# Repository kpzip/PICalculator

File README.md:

# *Award Winning* PICalculator
calculator made using super ancient PIC μController.

# Past customers have said:
"Fairly risky project that will depend a lot on the development environment. Not clear why 74HC138 will help read the buttons (could probably use SR for same purpose).         need to check what exists in terms of development environment    "This group chose the hardware as they "wanted a challenge". They are definitely one of the smarter groups in my section so I don't have much doubt that they will get it done. 

If you guys do think the hardware is more complex than neccesary, I'm sure they'd be okay with changing out the parts list."    "Are these people really experienced or did they find this project online? If the former, will all group members be able to contribute?

PIC16C74 likely does not have Arduino support. "ARM Cortex M4" is vague and any bare chip will likely only come in an SMD package. Both need a special programmer and special compiler setups. Would need to make a custom PCB or buy a dev board.

Why not just do everything in the M4 since it's vastly more powerful than the PIC?"    Looks like a very challenging project. I am not sure if all group members can contribute if they decide to go with this idea. I think one or two group members are pretty advanced. I feel like it would be hard to provide help to them since most mentors dont have experience with this microcontroller and it requires a different development environment.     Fairly sophisticated, were having issues with some operations outputting the wrong values"

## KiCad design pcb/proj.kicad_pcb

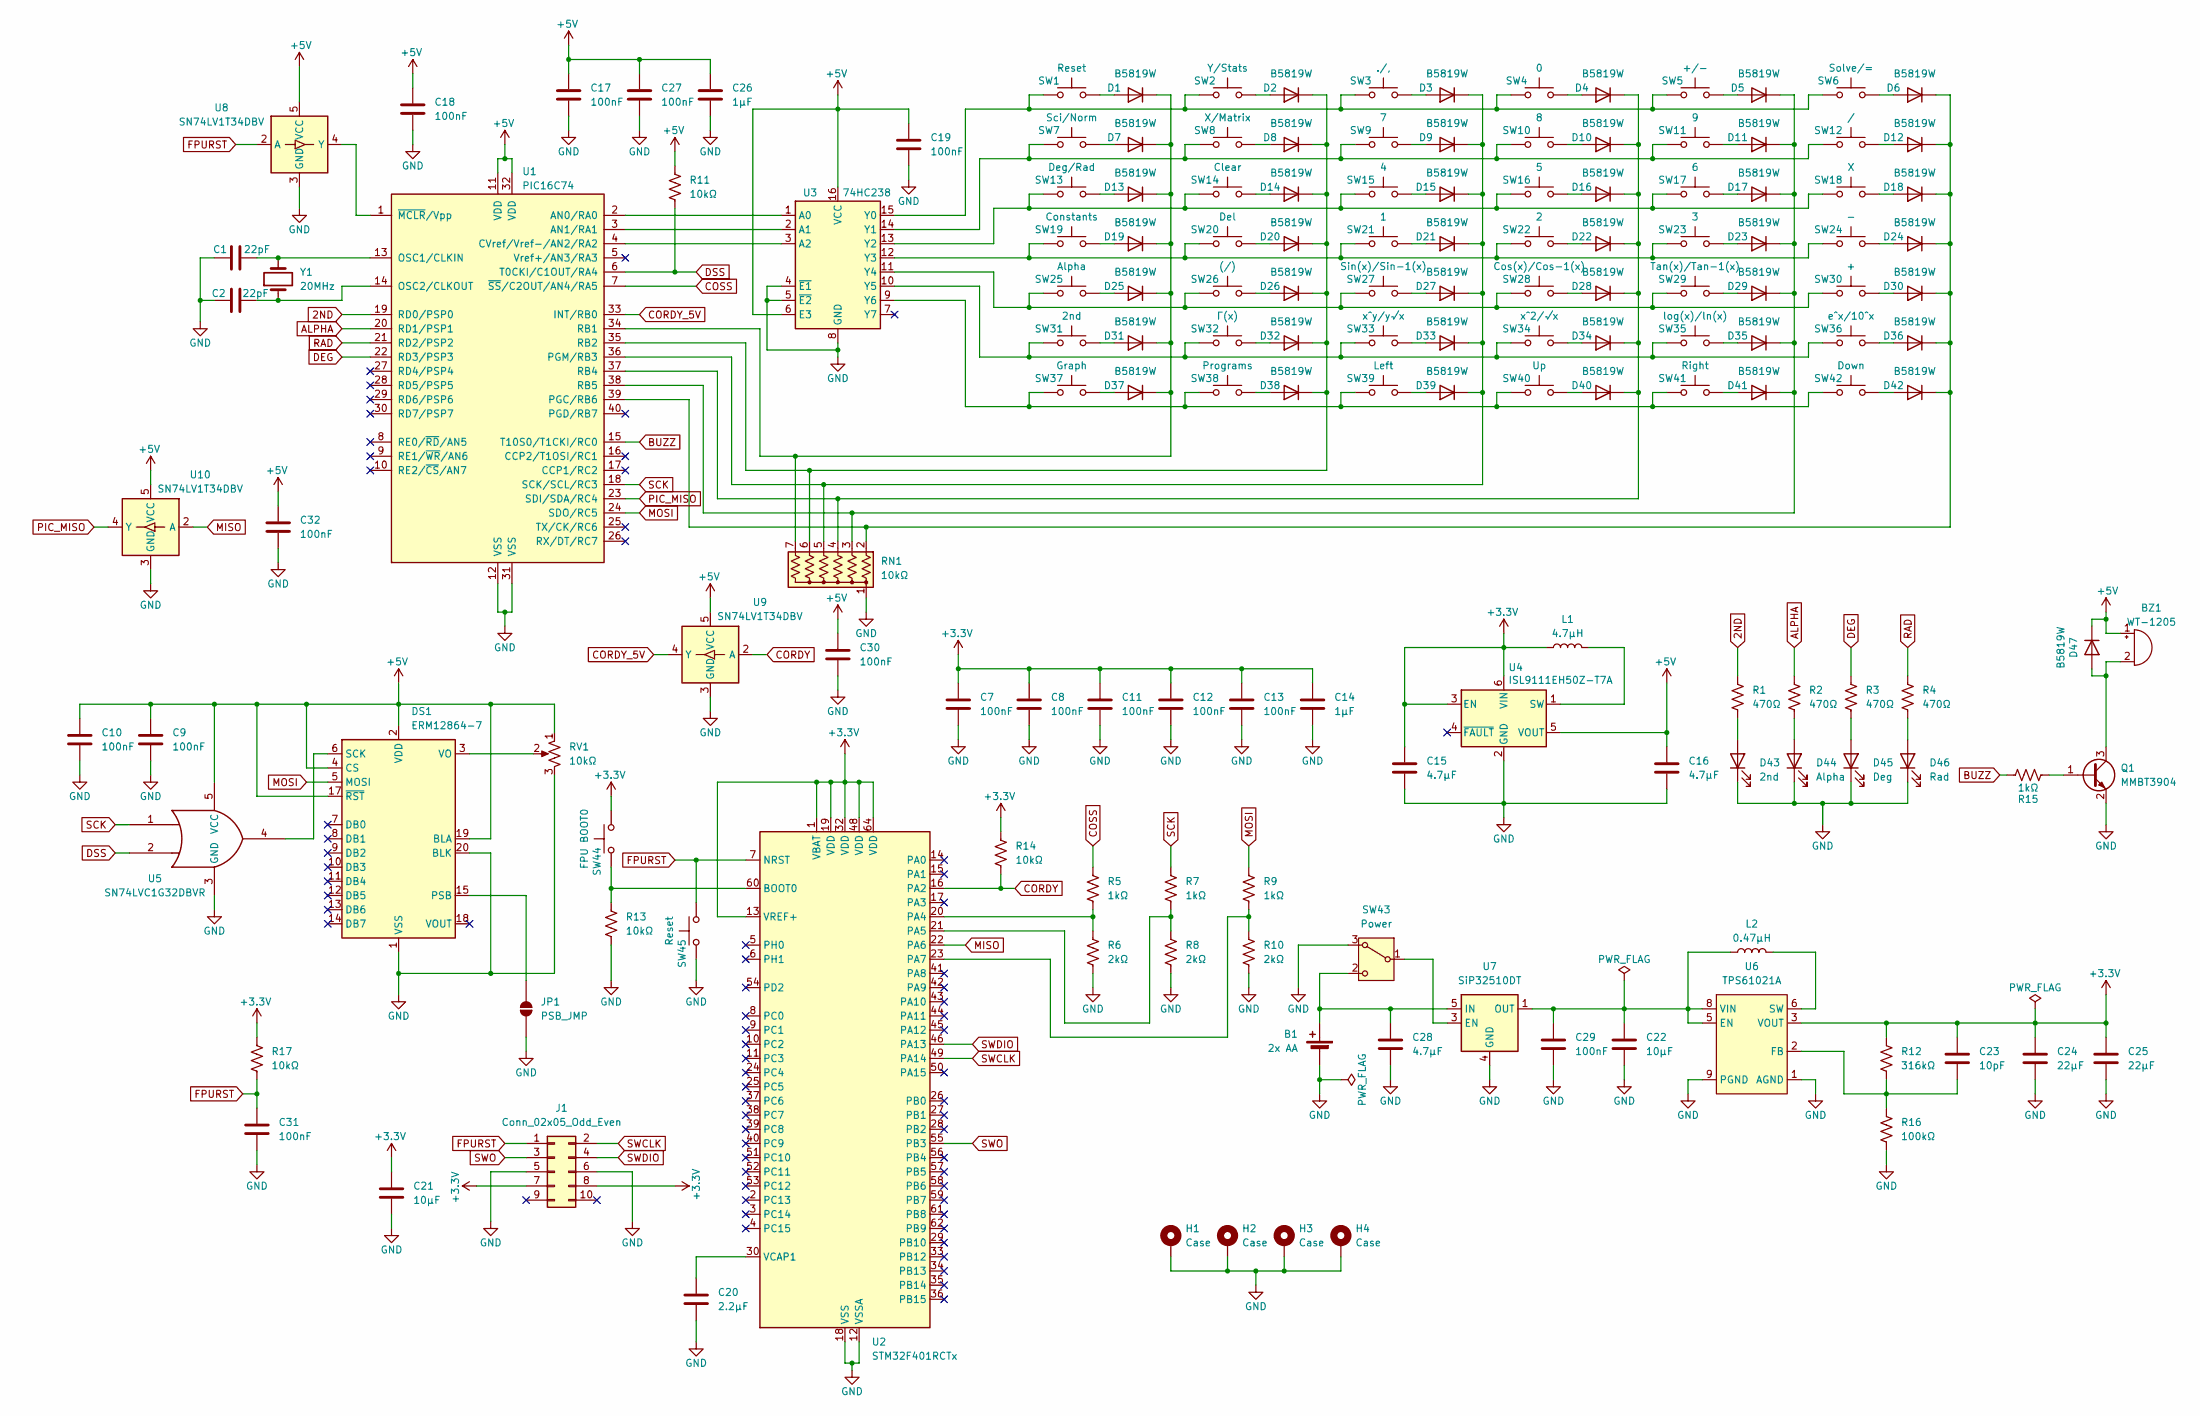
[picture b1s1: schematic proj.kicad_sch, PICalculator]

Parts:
B1: 2x AA; BatteryHolder_MPD_BC2AAPC_2xAA; Manufacturer Part Number BC2AAPC
BZ1: WT-1205; Buzzer_12x9.5RM7.6; Manufacturer Part Number AI-1223-TWT-5V-5-R
C1, C2: 22pF; C_0603_1608Metric; Manufacturer Part Number CL10C220JB8NNNC
C7, C8, C9, C10, C11, C12, C13, C17, C18, C19, C27, C29, C30, C31, C32: 100nF; C_0402_1005Metric; Manufacturer Part Number CL05B104KO5NNNC
C14, C26: 1μF; C_0603_1608Metric; Manufacturer Part Number CL10A105KB8NNNC
C15, C16, C28: 4.7μF; C_0603_1608Metric; Manufacturer Part Number CL10A475KO8NNNC
C20: 2.2μF; C_0603_1608Metric; Manufacturer Part Number CL10A225KO8NNNC
C21, C22: 10μF; C_0603_1608Metric; Manufacturer Part Number CL10A106MA8NRNC
C23: 10pF; C_0402_1005Metric; Manufacturer Part Number CL05C100JB5NNNC
C24, C25: 22μF; C_0603_1608Metric; Manufacturer Part Number CL10A226MQ8NRNC
D1, D2, D3, D4, D5, D6, D7, D8, D9, D10, D11, D12, D13, D14, D15, D16, D17, D18, D19, D20, D21, D22, D23, D24, D25, D26, D27, D28, D29, D30, D31, D32, D33, D34, D35, D36, D37, D38, D39, D40, D41, D42, D47: B5819W; D_SOD-123F; Manufacturer Part Number B5819W SL
D43: 2nd; LED_D5.0mm; Manufacturer Part Number WP7113ID
D44: Alpha; LED_D5.0mm; Manufacturer Part Number WP7113ID
D45: Deg; LED_D5.0mm; Manufacturer Part Number WP7113ID
D46: Rad; LED_D5.0mm; Manufacturer Part Number WP7113ID
DS1: ERM12864-7; Manufacturer Part Number ERM12864-7
H1, H2, H3, H4: Case; MountingHole_2.2mm_M2_ISO7380_Pad
J1: Conn_02x05_Odd_Even; IDC-Header_2x05_P2.54mm_Vertical; Manufacturer Part Number 302-S101
JP1: PSB_JMP; SolderJumper-2_P1.3mm_Open_RoundedPad1.0x1.5mm
L1: 4.7µH; L_1008_2520Metric_Pad1.43x2.20mm_HandSolder; Manufacturer Part Number FPB252012D-4R7MT0
L2: 0.47µH; L_Coilcraft_XxL4040; Manufacturer Part Number XFL4015-471MEC
Q1: MMBT3904; SOT-23; Manufacturer Part Number MMBT3904(RANGE:100-300)
R1, R2, R3, R4: 470Ω; R_Axial_DIN0207_L6.3mm_D2.5mm_P10.16mm_Horizontal; Manufacturer Part Number CF14JT470R
R5, R7, R9, R15: 1kΩ; R_0603_1608Metric; Manufacturer Part Number 0603WAF1001T5E
R6, R8, R10: 2kΩ; R_0603_1608Metric; Manufacturer Part Number 0603WAF2001T5E
R11, R13, R14, R17: 10kΩ; R_0603_1608Metric; Manufacturer Part Number 0603WAF1002T5E
R12: 316kΩ; R_0402_1005Metric; Manufacturer Part Number 0402WGF3163TCE
R16: 100kΩ; R_0402_1005Metric; Manufacturer Part Number 0402WGF1003TCE
RN1: 10kΩ; R_Array_SIP7; Manufacturer Part Number 4607X-101-103LF
RV1: 10kΩ; Potentiometer_Bourns_TC33X_Vertical; Manufacturer Part Number TC33X-1-103E
SW1, SW45: Reset; SW_PUSH_6mm; Manufacturer Part Number PTS645SL43-2 LFS
SW2: Y/Stats; SW_PUSH_6mm; Manufacturer Part Number PTS645SL43-2 LFS
SW3: ./,; SW_PUSH_6mm; Manufacturer Part Number PTS645SL43-2 LFS
SW4: 0; SW_PUSH_6mm; Manufacturer Part Number PTS645SL43-2 LFS
SW5: +/-; SW_PUSH_6mm; Manufacturer Part Number PTS645SL43-2 LFS
SW6: Solve/=; SW_PUSH_6mm; Manufacturer Part Number PTS645SL43-2 LFS
SW7: Sci/Norm; SW_PUSH_6mm; Manufacturer Part Number PTS645SL43-2 LFS
SW8: X/Matrix; SW_PUSH_6mm; Manufacturer Part Number PTS645SL43-2 LFS
SW9: 7; SW_PUSH_6mm; Manufacturer Part Number PTS645SL43-2 LFS
SW10: 8; SW_PUSH_6mm; Manufacturer Part Number PTS645SL43-2 LFS
SW11: 9; SW_PUSH_6mm; Manufacturer Part Number PTS645SL43-2 LFS
SW12: /; SW_PUSH_6mm; Manufacturer Part Number PTS645SL43-2 LFS
SW13: Deg/Rad; SW_PUSH_6mm; Manufacturer Part Number PTS645SL43-2 LFS
SW14: Clear; SW_PUSH_6mm; Manufacturer Part Number PTS645SL43-2 LFS
SW15: 4; SW_PUSH_6mm; Manufacturer Part Number PTS645SL43-2 LFS
SW16: 5; SW_PUSH_6mm; Manufacturer Part Number PTS645SL43-2 LFS
SW17: 6; SW_PUSH_6mm; Manufacturer Part Number PTS645SL43-2 LFS
SW18: X; SW_PUSH_6mm; Manufacturer Part Number PTS645SL43-2 LFS
SW19: Constants; SW_PUSH_6mm; Manufacturer Part Number PTS645SL43-2 LFS
SW20: Del; SW_PUSH_6mm; Manufacturer Part Number PTS645SL43-2 LFS
SW21: 1; SW_PUSH_6mm; Manufacturer Part Number PTS645SL43-2 LFS
SW22: 2; SW_PUSH_6mm; Manufacturer Part Number PTS645SL43-2 LFS
SW23: 3; SW_PUSH_6mm; Manufacturer Part Number PTS645SL43-2 LFS
SW24: -; SW_PUSH_6mm; Manufacturer Part Number PTS645SL43-2 LFS
SW25: Alpha; SW_PUSH_6mm; Manufacturer Part Number WP7113ID
SW26: (/); SW_PUSH_6mm; Manufacturer Part Number PTS645SL43-2 LFS
SW27: Sin(x)/Sin-1(x); SW_PUSH_6mm; Manufacturer Part Number PTS645SL43-2 LFS
SW28: Cos(x)/Cos-1(x); SW_PUSH_6mm; Manufacturer Part Number PTS645SL43-2 LFS
SW29: Tan(x)/Tan-1(x); SW_PUSH_6mm; Manufacturer Part Number PTS645SL43-2 LFS
SW30: +; SW_PUSH_6mm; Manufacturer Part Number PTS645SL43-2 LFS
SW31: 2nd; SW_PUSH_6mm; Manufacturer Part Number WP7113ID
SW32: Γ(x); SW_PUSH_6mm; Manufacturer Part Number PTS645SL43-2 LFS
SW33: x^y/y√x; SW_PUSH_6mm; Manufacturer Part Number PTS645SL43-2 LFS
SW34: x^2/√x; SW_PUSH_6mm; Manufacturer Part Number PTS645SL43-2 LFS
SW35: log(x)/ln(x); SW_PUSH_6mm; Manufacturer Part Number PTS645SL43-2 LFS
SW36: e^x/10^x; SW_PUSH_6mm; Manufacturer Part Number PTS645SL43-2 LFS
SW37: Graph; SW_PUSH_6mm; Manufacturer Part Number PTS645SL43-2 LFS
SW38: Programs; SW_PUSH_6mm; Manufacturer Part Number PTS645SL43-2 LFS
SW39: Left; SW_PUSH_6mm; Manufacturer Part Number PTS645SL43-2 LFS
SW40: Up; SW_PUSH_6mm; Manufacturer Part Number PTS645SL43-2 LFS
SW41: Right; SW_PUSH_6mm; Manufacturer Part Number PTS645SL43-2 LFS
SW42: Down; SW_PUSH_6mm; Manufacturer Part Number PTS645SL43-2 LFS
SW43: Power; SW_Slide-03_Wuerth-WS-SLTV_10x2.5x6.4_P2.54mm; Manufacturer Part Number EG1218
SW44: FPU BOOT0; SW_PUSH_6mm; Manufacturer Part Number PTS645SL43-2 LFS
U1: PIC16C74; DIP-40_W15.24mm_Socket_LongPads; Manufacturer Part Number PIC16C74
U2: STM32F401RCTx; LQFP-64_10x10mm_P0.5mm; Manufacturer Part Number STM32F401RCT6
U3: 74HC238; SOIC-16_3.9x9.9mm_P1.27mm; Manufacturer Part Number CD74HC238M96
U4: ISL9111EH50Z-T7A; SOT-23-6_Handsoldering
U5: SN74LVC1G32DBVR; SOT-23-5_HandSoldering; Manufacturer Part Number SN74LVC1G32DBVR
U6: TPS61021A; Texas_DSG0008A_WSON-8-1EP_2x2mm_P0.5mm_EP0.9x1.6mm; Manufacturer Part Number TPS61021ADSGR
U7: SiP32510DT; TSOT-23-6; Manufacturer Part Number SIP32510DT-T1-GE3
U8, U9, U10: SN74LV1T34DBV; SOT-23-5; Manufacturer Part Number SN74LV1T34DBVR
Y1: 20MHz; Crystal_HC49-U_Vertical; Manufacturer Part Number AS-20.000-20

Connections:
2ND: R1.1, U1.19 (RD0/PSP0)
+3.3V: C7.1, C8.1, C11.1, C12.1, C13.1, C14.1, C15.1, C21.1, C23.1, C24.1, C25.1, J1.7, J1.8, L1.1, R12.1, R14.1, R17.1, SW44.2, U2.1 (VBAT), U2.13 (VREF+), U2.19 (VDD), U2.32 (VDD), U2.48 (VDD), U2.64 (VDD), U4.3 (EN), U4.6 (VIN), U6.3 (VOUT), U6.4 (VOUT)
+5V: BZ1.1 (+), C9.1, C10.1, C16.1, C17.1, C18.1, C19.1, C26.1, C27.1, C30.1, C32.1, D47.1 (K), DS1.2 (VDD), DS1.4 (CS), DS1.17 (~RST), DS1.19 (BLA), R11.1, RV1.1, U1.11 (VDD), U1.32 (VDD), U3.6 (E3), U3.16 (VCC), U4.5 (VOUT), U5.5 (VCC), U8.5 (VCC), U9.5 (VCC), U10.5 (VCC)
ALPHA: R2.1, U1.20 (RD1/PSP1)
BUZZ: R15.1, U1.15 (T10S0/T1CKI/RC0)
CORDY: R14.2, U2.16 (PA2), U9.2 (A)
CORDY_5V: U1.33 (INT/RB0), U9.4 (Y)
COSS: R5.1, U1.7 (~SS/C2OUT/AN4/RA5)
DEG: R3.1, U1.22 (RD3/PSP3)
DSS: R11.2, U1.6 (T0CKI/C1OUT/RA4), U5.2
FPURST: C31.1, J1.1, R17.2, SW45.2, U2.7 (NRST), U8.2 (A)
GND: B1.2 (-), C1.1, C2.1, C7.2, C8.2, C9.2, C10.2, C11.2, C12.2, C13.2, C14.2, C15.2, C16.2, C17.2, C18.2, C19.2, C20.2, C21.2, C22.2, C24.2, C25.2, C26.2, C27.2, C28.2, C29.2, C30.2, C31.2, C32.2, D43.1 (K), D44.1 (K), D45.1 (K), D46.1 (K), DS1.1 (VSS), DS1.20 (BLK), H1.1 (1_1), H2.1 (1_1), H3.1 (1_1), H4.1 (1_1), J1.5, J1.6, JP1.1 (A), Q1.2 (E), R6.2, R8.2, R10.2, R13.2, R16.2, RN1.1 (common), RV1.3, SW43.3 (A), SW45.1, U1.12 (VSS), U1.31 (VSS), U2.12 (VSSA), U2.18 (VSS), U2.31 (VSS), U2.47 (VSS), U2.63 (VSS), U3.4 (~E1), U3.5 (~E2), U3.8 (GND), U4.2 (GND), U5.3 (GND), U6.1 (AGND), U6.9 (PGND), U7.4 (GND), U8.3 (GND), U9.3 (GND), U10.3 (GND)
MISO: U2.22 (PA6), U10.2 (A)
MOSI: DS1.5 (MOSI), R9.1, U1.24 (SDO/RC5)
unnamed: B1.1 (+), C28.1, SW43.2 (C), U7.5 (IN), U7.6 (IN)
unnamed: BZ1.2 (-), D47.2 (A), Q1.3 (C)
unnamed: D1.2 (A), SW1.2
unnamed: D1.1 (K), D7.1 (K), D13.1 (K), D19.1 (K), D25.1 (K), D31.1 (K), D37.1 (K), RN1.7 (R6), U1.34 (RB1)
unnamed: D2.2 (A), SW2.2
unnamed: D3.2 (A), SW3.2
unnamed: D4.2 (A), SW4.2
unnamed: D5.2 (A), SW5.2
unnamed: D6.2 (A), SW6.2
unnamed: D7.2 (A), SW7.2
unnamed: D8.2 (A), SW8.2
unnamed: D9.2 (A), SW9.2
unnamed: D10.2 (A), SW10.2
unnamed: D4.1 (K), D10.1 (K), D16.1 (K), D22.1 (K), D28.1 (K), D34.1 (K), D40.1 (K), RN1.4 (R3), U1.37 (RB4)
unnamed: D11.2 (A), SW11.2
unnamed: D5.1 (K), D11.1 (K), D17.1 (K), D23.1 (K), D29.1 (K), D35.1 (K), D41.1 (K), RN1.3 (R2), U1.38 (RB5)
unnamed: D12.2 (A), SW12.2
unnamed: D6.1 (K), D12.1 (K), D18.1 (K), D24.1 (K), D30.1 (K), D36.1 (K), D42.1 (K), RN1.2 (R1), U1.39 (PGC/RB6)
unnamed: D13.2 (A), SW13.2
unnamed: D14.2 (A), SW14.2
unnamed: D2.1 (K), D8.1 (K), D14.1 (K), D20.1 (K), D26.1 (K), D32.1 (K), D38.1 (K), RN1.6 (R5), U1.35 (RB2)
unnamed: D15.2 (A), SW15.2
unnamed: D3.1 (K), D9.1 (K), D15.1 (K), D21.1 (K), D27.1 (K), D33.1 (K), D39.1 (K), RN1.5 (R4), U1.36 (PGM/RB3)
unnamed: D16.2 (A), SW16.2
unnamed: D17.2 (A), SW17.2
unnamed: D18.2 (A), SW18.2
unnamed: D19.2 (A), SW19.2
unnamed: D20.2 (A), SW20.2
unnamed: D21.2 (A), SW21.2
unnamed: D22.2 (A), SW22.2
unnamed: D23.2 (A), SW23.2
unnamed: D24.2 (A), SW24.2
unnamed: D25.2 (A), SW25.2
unnamed: D26.2 (A), SW26.2
unnamed: D27.2 (A), SW27.2
unnamed: D28.2 (A), SW28.2
unnamed: D29.2 (A), SW29.2
unnamed: D30.2 (A), SW30.2
unnamed: D31.2 (A), SW31.2
unnamed: D32.2 (A), SW32.2
unnamed: D33.2 (A), SW33.2
unnamed: D34.2 (A), SW34.2
unnamed: D35.2 (A), SW35.2
unnamed: D36.2 (A), SW36.2
unnamed: D37.2 (A), SW37.2
unnamed: D38.2 (A), SW38.2
unnamed: D39.2 (A), SW39.2
unnamed: D40.2 (A), SW40.2
unnamed: D41.2 (A), SW41.2
unnamed: D42.2 (A), SW42.2
unnamed: D43.2 (A), R1.2
unnamed: D44.2 (A), R2.2
unnamed: D45.2 (A), R3.2
unnamed: D46.2 (A), R4.2
unnamed: DS1.15 (PSB), JP1.2 (B)
unnamed: DS1.6 (SCK), U5.4
unnamed: DS1.3 (VO), RV1.2
unnamed: L2.2, U6.6 (SW), U6.7 (SW)
unnamed: Q1.1 (B), R15.2
unnamed: SW43.1 (B), U7.3 (EN)
unnamed: U1.2 (AN0/RA0), U3.1 (A0)
unnamed: U1.3 (AN1/RA1), U3.2 (A1)
unnamed: U1.4 (CVref/Vref-/AN2/RA2), U3.3 (A2)
unnamed: C1.2, U1.13 (OSC1/CLKIN), Y1.2
unnamed: C2.2, U1.14 (OSC2/CLKOUT), Y1.1
unnamed: U1.1 (~MCLR/Vpp), U8.4 (Y)
unnamed: R13.1, SW44.1, U2.60 (BOOT0)
unnamed: R5.2, R6.1, U2.20 (PA4)
unnamed: R7.2, R8.1, U2.21 (PA5)
unnamed: R9.2, R10.1, U2.23 (PA7)
unnamed: C20.1, U2.30 (VCAP1)
unnamed: SW1.1, SW2.1, SW3.1, SW4.1, SW5.1, SW6.1, U3.15 (Y0)
unnamed: SW7.1, SW8.1, SW9.1, SW10.1, SW11.1, SW12.1, U3.14 (Y1)
unnamed: SW13.1, SW14.1, SW15.1, SW16.1, SW17.1, SW18.1, U3.13 (Y2)
unnamed: SW19.1, SW20.1, SW21.1, SW22.1, SW23.1, SW24.1, U3.12 (Y3)
unnamed: SW25.1, SW26.1, SW27.1, SW28.1, SW29.1, SW30.1, U3.11 (Y4)
unnamed: SW31.1, SW32.1, SW33.1, SW34.1, SW35.1, SW36.1, U3.10 (Y5)
unnamed: SW37.1, SW38.1, SW39.1, SW40.1, SW41.1, SW42.1, U3.9 (Y6)
unnamed: L1.2, U4.1 (SW)
unnamed: C22.1, C29.1, L2.1, U6.5 (EN), U6.8 (VIN), U7.1 (OUT), U7.2 (OUT)
unnamed: C23.2, R12.2, R16.1, U6.2 (FB)
PIC_MISO: U1.23 (SDI/SDA/RC4), U10.4 (Y)
RAD: R4.1, U1.21 (RD2/PSP2)
SCK: R7.1, U1.18 (SCK/SCL/RC3), U5.1
SWCLK: J1.2, U2.49 (PA14)
SWDIO: J1.4, U2.46 (PA13)
SWO: J1.3, U2.55 (PB3)

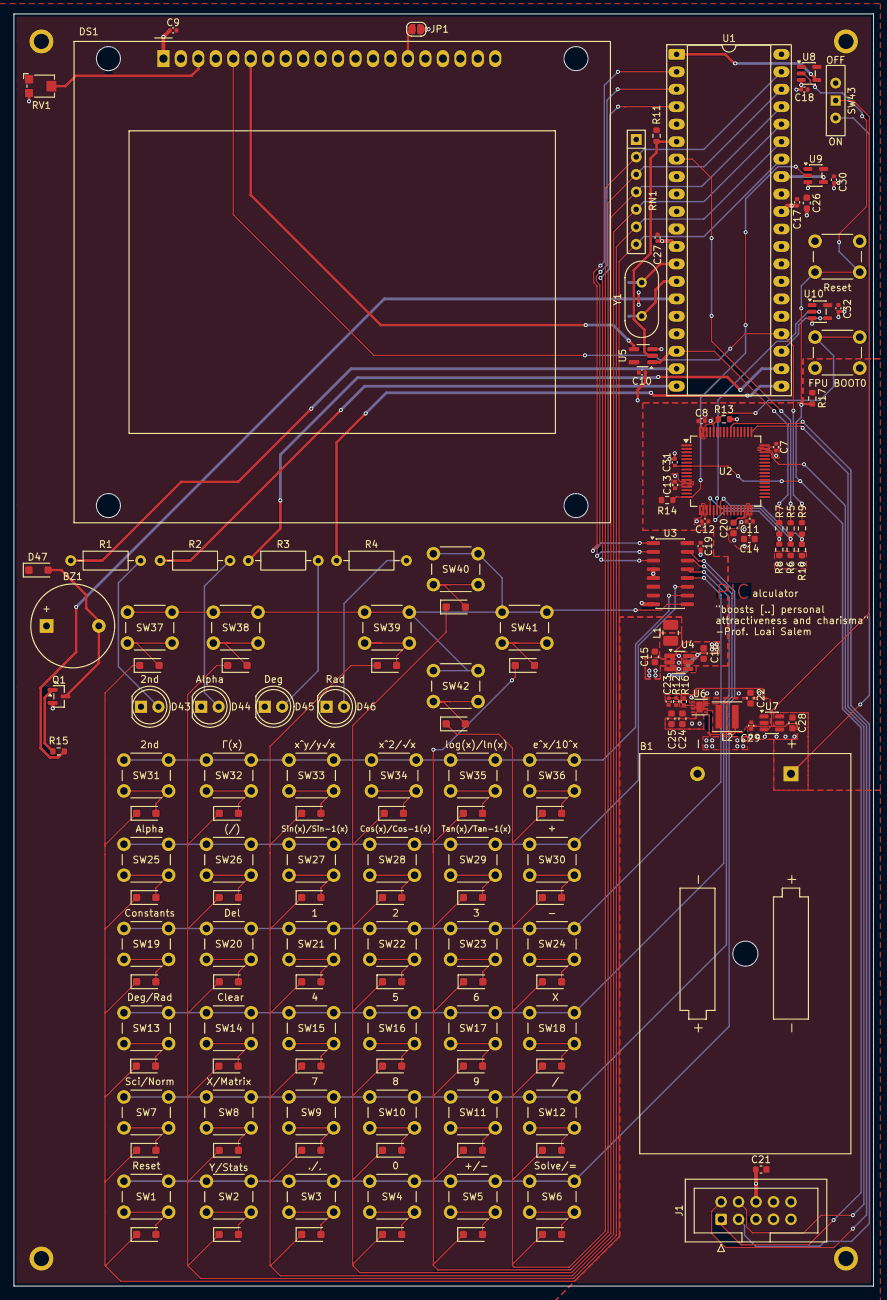
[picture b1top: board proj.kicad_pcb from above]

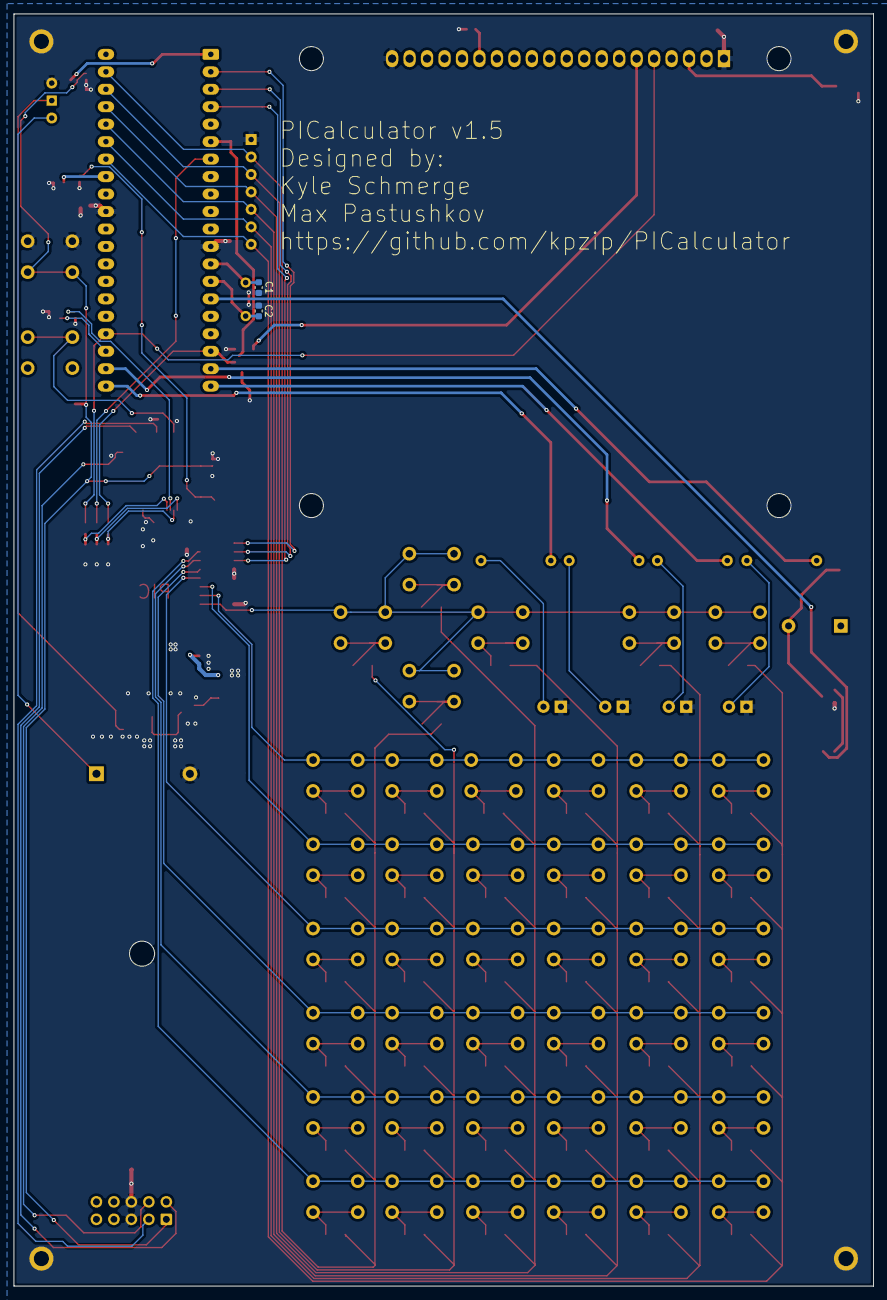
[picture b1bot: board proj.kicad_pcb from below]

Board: 2 copper layers, 125.0 x 185.0 mm, 162 parts (2 on the bottom side), 101 nets.

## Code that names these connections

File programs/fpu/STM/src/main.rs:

#![allow(clippy::empty_loop)]
#![no_main]
#![no_std]

mod gui;
mod keymaps;
mod util;

extern crate alloc;
extern crate panic_halt;

use alloc::string::ToString;
use core::ops::{Deref, DerefMut};

use crate::hal::{pac, prelude::*};
use cortex_m_rt::entry;
use hal::gpio::alt::spi1::Nss;
use hal::spi::{Mode, Phase, Polarity};
use rtt_target::{rprintln, rtt_init_print};
use stm32f4xx_hal as hal;
use gui::{CalculatorMenu, CalculatorState, sci_error, sci_mode};
use embedded_alloc::LlffHeap as Heap;
use stm32f4xx_hal::flash::{FlashExt, LockedFlash};
use stm32f4xx_hal::gpio::Pin;
use stm32f4xx_hal::hal::digital::OutputPin;
use stm32f4xx_hal::spi::{Instance, SpiSlave};

#[global_allocator]
static HEAP: Heap = Heap::empty();

#[entry]
fn main() -> ! {
    rtt_init_print!();

    // Initialize the allocator BEFORE you use it
    {
        use core::mem::MaybeUninit;
        const HEAP_SIZE: usize = 1024 * 4;
        static mut HEAP_MEM: [MaybeUninit<u8>; HEAP_SIZE] = [MaybeUninit::uninit(); HEAP_SIZE];
        unsafe { HEAP.init(&raw mut HEAP_MEM as usize, HEAP_SIZE) }
    }

    let dp = pac::Peripherals::take().unwrap();
    let cp = cortex_m::Peripherals::take().unwrap();

    // let flash = dp.FLASH;
    // flash.acr().modify(|_r, w| unsafe {
    //     w.latency().bits(0b1111)
    // });

    let gpioa = dp.GPIOA.split();

    // Set up the system clock. We want to run at 48MHz for this one.
    let rcc = dp.RCC.constrain();
    let clocks = rcc.cfgr.sysclk(48.MHz()).freeze();



    // Create a delay abstraction based on SysTick
    let mut delay = cp.SYST.delay(&clocks);

    let mut ready = gpioa.pa2.into_push_pull_output();
    ready.set_low();

    let sck = gpioa.pa5;
    let mut miso = gpioa.pa6;
    let mosi = gpioa.pa7;
    let nss = gpioa.pa4;

    let mut spi = dp.SPI1.spi_slave(
        (sck, miso, mosi, Some(Nss::from(nss))),
        Mode {
            phase: Phase::CaptureOnSecondTransition,
            polarity: Polarity::IdleHigh,
        },
    );

    // Buffer for reading in SPI data
    let mut data: [u8; 2] = [0; 2];

    // Calc State
    let mut calc_state = CalculatorState::new();

    loop {

        match spi.read(&mut data) {
            Ok(()) => {
                rprintln!("Received data: {:02X?}", data);
                // Key press code
                if data[0] == 1 {
                    rprintln!("Handling Key Press!");
                    let key_id = data[1];
                    gui::handle_button_press(key_id, &mut calc_state);
                    gui::update_gui(&mut calc_state, &mut spi, &mut ready);
                    rprintln!("Done!");
                } else {
                    rprintln!("Error Unknown Request: {:02X?}", data);
                    reset_pic_interface(&mut spi, &mut ready);
                    continue;
                }
            }
            Err(e) => {
                rprintln!("Error: {:?}", e);
                reset_pic_interface(&mut spi, &mut ready);
            }
        }
    }
}

fn reset_pic_interface<SPI: Instance, MODE, const L: char, const N: u8>(
spi: &mut SpiSlave<SPI>,
ready: &mut Pin<L, N, MODE>,
) where
Pin<L, N, MODE>: OutputPin
{
    let _ = ready.set_high();
    let _ = spi.write(&[0x00]);
    let _ = ready.set_low();
}

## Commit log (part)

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2024-12-13 init
2024-12-13 Add PIC16 folder
2024-12-13 embedded
2024-12-13 Comment stuff out
2024-12-13 Edit more bullshit to make it error out slightly later :/
2024-12-13 Many more errors
2024-12-13 Obliterate unnecessary(?) files
2025-01-10 Fuck around more
2025-01-10 AAAAAAA
2025-01-11 We do a little DAGing
2025-01-12 It compiles! (Doesn't fucking link)
2025-01-13 Generate a thousand linker errors and fix some of them
2025-01-13 IT BUILD!!!
2025-01-13 Fix debug info
2025-01-13 cmake
2025-01-13 hellos world
2025-01-14 Fix (not)
2025-01-14 cmake crap
2025-01-14 begin progress on emulator
2025-01-14 Fix stack overflow
2025-01-19 switch to C++
2025-01-19 add all cpp files to exe
2025-01-19 standard lib stuff
2025-01-19 instruction set
2025-01-19 initialize constants
2025-01-19 cppify
2025-01-19 work on deserializing stuff
2025-01-19 head down to the pub get a pint with the lads
2025-01-19 NOP will always be zero in our hearts
2025-01-19 macro it up
2025-01-19 instruction matching for opcodes
2025-01-19 fix opcode handling
2025-01-19 fix for CALL and GOTO instructions
2025-01-19 add to h file
2025-01-19 program mem + start thinking about using oop
2025-01-20 refactor
2025-01-20 major refactor
2025-01-23 Start redesigning registers
2025-01-24 stuff
2025-01-24 moved PIC folder to other repo
2025-02-05 fix gitignore
2025-02-05 ignore locks
2025-02-06 work
2025-02-18 work on qt
2025-02-25 Add MPLAB project file
2025-02-25 get it working
2025-02-26 2nd alpha and deg/rad
2025-02-26 fix issues
2025-02-26 fix indents
2025-03-02 init cargo project
2025-03-02 fix memory issues
2025-03-02 pcb work
2025-03-03 testing
2025-03-03 progress
2025-03-04 work on graph function
2025-03-05 board
2025-03-06 Fixes
2025-03-06 ignore file
2025-03-06 remove cache file
2025-03-06 minor updates
2025-03-10 rename stuff
2025-03-10 initialize project for pic passthrough
2025-03-10 make single op expressions work
2025-03-11 archive v1.1
2025-03-11 joao mode
2025-03-12 work on graphing
2025-03-12 works maybe?
2025-03-12 change delay
2025-03-12 UB more like gone
2025-03-12 NO MORE UB!!!!!
2025-03-12 function sig
2025-03-13 test
2025-03-13 its 1 am bruh
2025-03-13 fix????
2025-03-13 fix stuff
2025-03-13 works????!?!!?!!!!!
2025-03-14 add startup delay
2025-03-29 make 16 bit arithmetic work
2025-04-05 deliverables
2025-04-06 UB more like VB
2025-04-07 v 1.2
2025-04-09 Graphing works (finally)
2025-04-10 Change STM communication protocol
2025-04-10 Make it work
2025-04-15 update schematics + add CO RDY trace
2025-04-16 Rust working on STM
2025-04-18 Make it kinda work
2025-04-19 shiftreduce
2025-04-19 fix panicking
2025-04-19 add buzzer and join resets
2025-04-20 make everything better
2025-04-20 cursor shenanigans
2025-04-21 fix bugs with passthrough mode
2025-04-21 remove unnecessary stuff
2025-04-21 more work
2025-04-21 clean
2025-04-21 file structure
2025-04-22 other functions
2025-04-25 graph!!!
2025-04-30 scaling
2025-05-09 constants work
2025-05-14 v1.2
2025-05-29 archive 1.3
2025-05-29 false alarm
2025-06-02 add titles
2025-06-03 archive
2025-06-22 stupid nub
2025-07-02 debug spi
